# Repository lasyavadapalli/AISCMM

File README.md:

# AISCMM
The final year project repository
This Repository contains following set of folders

## 1. IEEE_Papers_Refered
This folder contains the IEEE papaers we refered for the implementation of the project.

## 2. MOM
This folder contains the minutes of meetings.

## 3. PPT 
This folder contains the presentations that were dilevered in the TIFR as well as in the college

## 4. Pcb_Layouts
This folder contains the pcb layouts that we created for the raspberry pi and the NodeMCU.

## 5. Project_Manual
This folder contains the copy of cookbooks, abtract, report, IEEE paper and some datasheets. The cookbooks are present in the CookBook folder inside this directory.

## 6. src
This is the folder which contains the code to be installed from the GitHub. This folder contains the subfolder for each type of code.

## Steps to install the project:
### Using Clone or Download Option
One can directly download the zip file from clone or download option present on the right hand side of the screen. Once the entire project is downloaded one can install the individual components of the project by refering individual readme files.

### Using Git bash:
The git bash can be used to download the project with git commands. The prerequisite is to have git installed in the system. The following set of commands are for downloading project on the windows operating system:-
* Create the empty folder and open git bash from it by right click and then open git bash from here. 

* Once the git bash is opened, clone the project in the current directory using the command:
```
git clone https://github.com/cw-rashmi/AISCMM.git
```
Once the clonning is complete your Desktop will contain all files present on GitHub.

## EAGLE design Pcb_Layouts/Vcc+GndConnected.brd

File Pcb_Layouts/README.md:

# PCB Layouts
This folder contains all pcb layouts made till date.

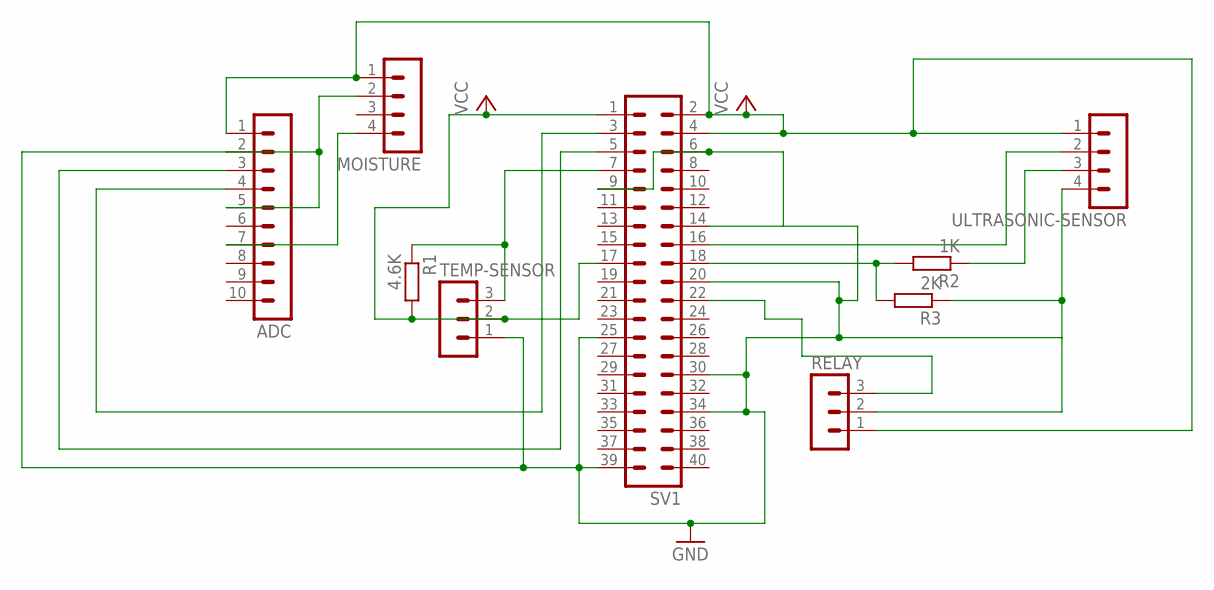
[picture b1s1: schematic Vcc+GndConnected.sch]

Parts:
ADC: MA10-1
MOISTURE: MA04-1
R1: 4.6K; 0207/10
R2: 1K; 0207/10
R3: 2K; 0207/10
RELAY: MA03-1
SV1: MA20-2
TEMP-SENSOR: MA03-1
ULTRASONIC-SENSOR: MA04-1

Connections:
GND: ADC.2, ADC.5, MOISTURE.2, R3.1, RELAY.2, SV1.6, SV1.9, SV1.14, SV1.20, SV1.25, SV1.30, SV1.34, SV1.39, TEMP-SENSOR.1, ULTRASONIC-SENSOR.4
unnamed: R2.1, ULTRASONIC-SENSOR.3
unnamed: SV1.16, ULTRASONIC-SENSOR.2
unnamed: R2.2, R3.2, SV1.18
unnamed: ADC.3, SV1.5
unnamed: ADC.4, SV1.3
unnamed: ADC.7, MOISTURE.4
unnamed: RELAY.3, SV1.22
unnamed: R1.1, SV1.7, TEMP-SENSOR.3
VCC: ADC.1, MOISTURE.1, R1.2, RELAY.1, SV1.1, SV1.2, SV1.4, SV1.17, TEMP-SENSOR.2, ULTRASONIC-SENSOR.1

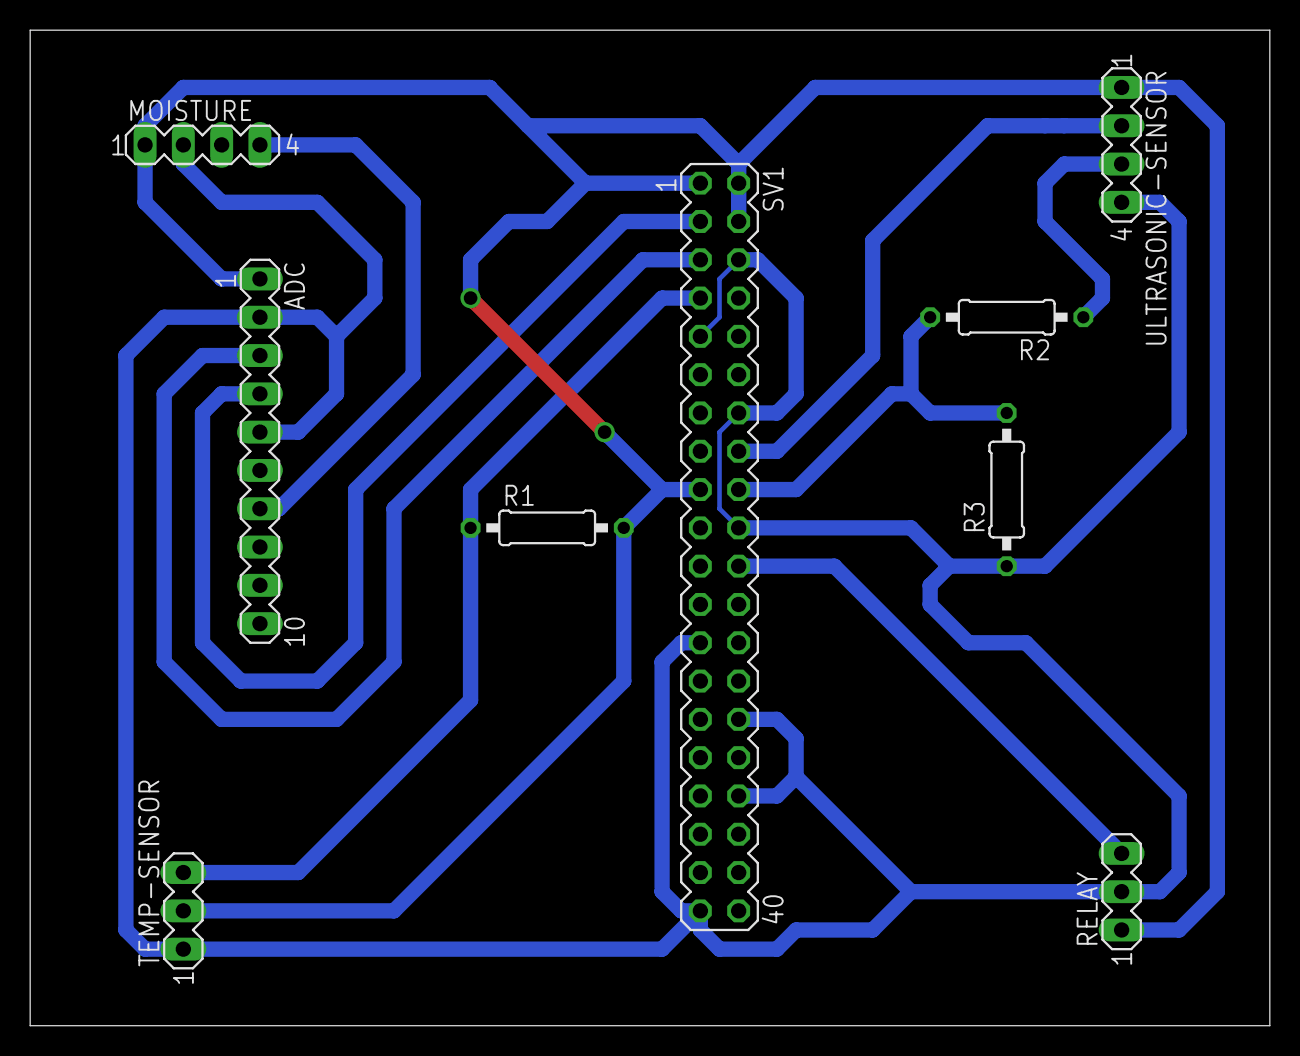
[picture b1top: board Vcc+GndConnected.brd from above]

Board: 2 copper layers, 82.2 x 66.0 mm, 9 parts (0 on the bottom side), 10 nets.

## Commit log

2019-04-17 Adding Flask server data
2019-04-17 Updating the Mobile application
2019-04-17 Added ppts
2019-04-17 Added NodeMCU code
2019-04-17 Adding readme files
2019-04-17 Added images for RPi
2019-04-17 First update to the readme file of raspberry pi
2019-04-17 Added the pics to the readme
2019-04-17 Added pic1
2019-04-17 Added all pics of putty
2019-04-17 Updating readme
2019-04-17 Added all pics of rpi
2019-04-17 Changes in readme file
2019-04-17 Only few pics are remaining
2019-04-17 Adding pics of NodeMCU
2019-04-17 Added the content of the NodeMCU readme file
2019-04-17 Added the pics in the readme file of NodeMCU
2019-04-17 Removing image defects
2019-04-17 Changing Alignment in readme file
2019-04-17 Adding IEEE Papers
2019-04-17 Adding MOM's
2019-04-17 Adding Pcb Layouts
2019-04-17 Adding PPTs Project Manual
2019-04-17 Updated readme file of MOM
2019-04-17 Updating the presentations of project
2019-04-17 Updated the readme file of PCB layout
2019-04-17 Updated readme file of Manual
2019-04-17 Updated the readme file of the IEEE papers
2019-04-17 Updated the readme file of the SRC folder
2019-04-17 Added the content of readme file.
2019-04-17 Updated the readme file of flask server
2019-04-19 Adding the information about the folders
2019-04-19 Adding information about the machines.
2019-04-19 Added the OS details
2019-04-19 Added information about the packages
2019-04-19 Added cookbook
2019-04-19 Adding the directions to download the project
2019-04-23 Updating the mobile app code
2019-04-23 Added the commands for SHA-1 certificate key
2019-04-23 Adding the build instructions
